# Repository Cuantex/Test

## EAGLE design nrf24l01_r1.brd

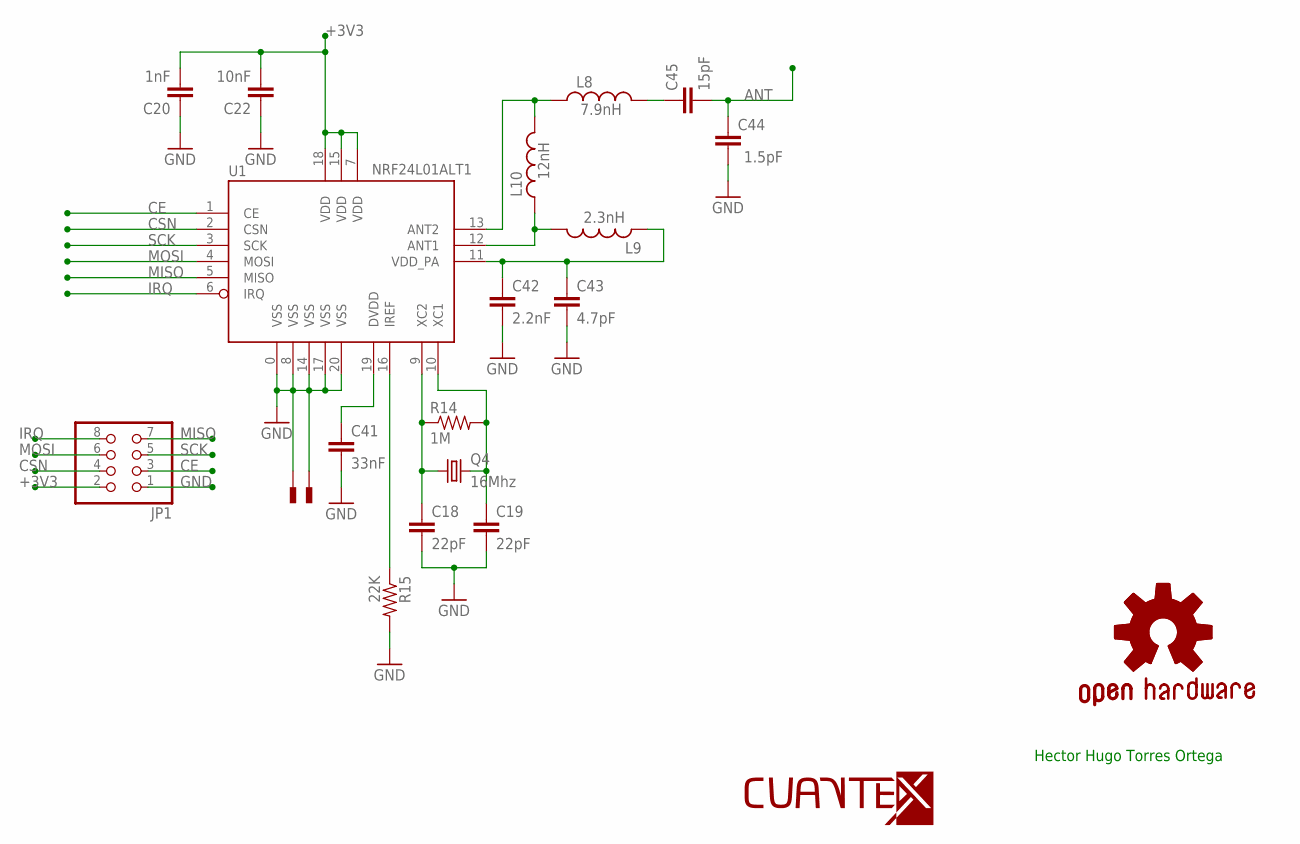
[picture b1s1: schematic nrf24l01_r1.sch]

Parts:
C18, C19: 22pF; 0402-CAP
C20: 1nF; 0402-CAP
C22: 10nF; 0402-CAP
C41: 33nF; 0402-CAP
C42: 2.2nF; 0402-CAP
C43: 4.7pF; 0402-CAP
C44: 1.5pF; 0402-CAP
C45: 15pF; 0402-CAP
GOLD_ORB_SM1: OSHWLOGO_GOLD_ORB_SM; OSHW2
JP1: PINHD-2X4; 2X04
L8: 7.9nH; C0402
L9: 2.3nH; C0402
L10: 12nH; C0402
Q4: 16Mhz; HC49/S
R14: 1M; 0402-RES
R15: 22K; 0402-RES
U1: NRF24L01ALT1; QFN20_ALT1
U$1: LOGO-BOT-20MM; B-20
U$9, U$10: PAD; PAD-0.008

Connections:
+3V3: C20.2, C22.2, JP1.2, U1.7 (VDD), U1.15 (VDD), U1.18 (VDD)
ANT: C44.2, C45.2
CE: JP1.3, U1.1 (CE)
CSN: JP1.4, U1.2 (CSN)
GND: C18.2, C19.2, C20.1, C22.1, C41.2, C42.2, C43.2, C44.1, JP1.1, R15.2, U1.0 (VSS), U1.8 (VSS), U1.14 (VSS), U1.17 (VSS), U1.20 (VSS), U$9.P$1, U$10.P$1
IRQ: JP1.8, U1.6 (IRQ)
MISO: JP1.7, U1.5 (MISO)
MOSI: JP1.6, U1.4 (MOSI)
unnamed: C18.1, Q4.1, R14.1, U1.9 (XC2)
unnamed: C19.1, Q4.2, R14.2, U1.10 (XC1)
unnamed: L8.1, L10.2, U1.13 (ANT2)
unnamed: C42.1, C43.1, L9.1, U1.11 (VDD_PA)
unnamed: R15.1, U1.16 (IREF)
unnamed: C41.1, U1.19 (DVDD)
unnamed: L9.2, L10.1, U1.12 (ANT1)
unnamed: C45.1, L8.2
SCK: JP1.5, U1.3 (SCK)

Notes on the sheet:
Hector Hugo Torres Ortega

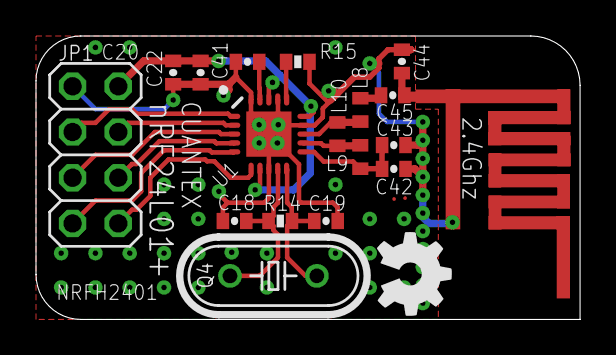
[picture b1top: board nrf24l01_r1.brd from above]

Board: 2 copper layers, 30.2 x 15.7 mm, 21 parts (0 on the bottom side), 17 nets.

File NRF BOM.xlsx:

Qty | Value | Device | Package | Parts | Description
1 |  | PINHD-2X4 | 2X04 | JP1 | PIN HEADER
1 | 1.5pF | CAP0402-CAP | 0402-CAP | C44 | Capacitor
1 | 10nF | CAP0402-CAP | 0402-CAP | C22 | Capacitor
1 | 12nH | INDUCTOR0402 | C0402 | L10 | Inductors
1 | 15pF | CAP0402-CAP | 0402-CAP | C45 | Capacitor
1 | 16Mhz | CRYSTALHC49S | HC49/S | Q4 | CRYSTAL
1 | 1M | RESISTOR0402-RES | 0402-RES | R14 | Resistor
1 | 1nF | CAP0402-CAP | 0402-CAP | C20 | Capacitor
1 | 2.2nF | CAP0402-CAP | 0402-CAP | C42 | Capacitor
1 | 2.3nH | INDUCTOR0402 | C0402 | L9 | Inductors
1 | 22K | RESISTOR0402-RES | 0402-RES | R15 | Resistor
2 | 22pF | CAP0402-CAP | 0402-CAP | C18, C19 | Capacitor
1 | 33nF | CAP0402-CAP | 0402-CAP | C41 | Capacitor
1 | 4.7pF | CAP0402-CAP | 0402-CAP | C43 | Capacitor
1 | 7.9nH | INDUCTOR0402 | C0402 | L8 | Inductors
1 | NRF24L01ALT1 | NRF24L01ALT1 | QFN20_ALT1 | U1 | 2.4GHz Low Power Transceiver
2 | PAD | PAD | PAD-0.008 | U$9, U$10
